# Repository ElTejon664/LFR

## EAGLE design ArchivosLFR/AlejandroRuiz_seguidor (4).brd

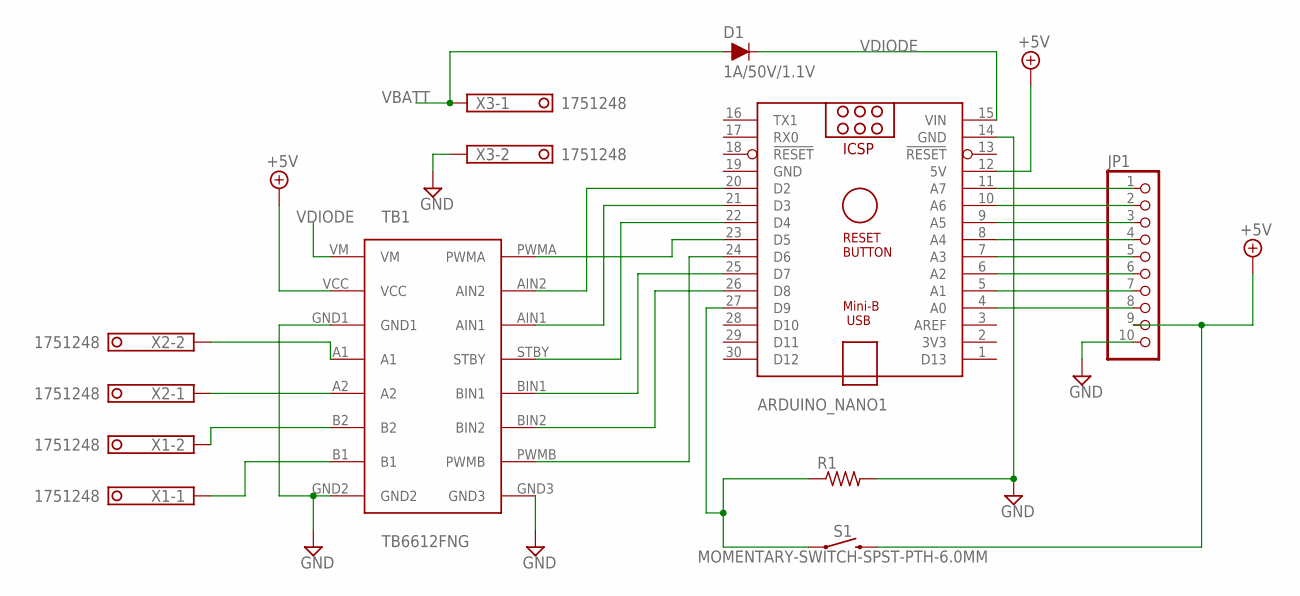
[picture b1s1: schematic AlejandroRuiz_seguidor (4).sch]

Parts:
ARDUINO_NANO1: ARDUINO_NANO
D1: 1A/50V/1.1V; DIODE-1N4001
JP1: PINHD-1X10; 1X10
R1: R-US_0204/5; 0204/5
S1: MOMENTARY-SWITCH-SPST-PTH-6.0MM; TACTILE_SWITCH_PTH_6.0MM
TB1: TB6612FNG
X1, X2, X3: 1751248

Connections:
+5V: ARDUINO_NANO1.12 (5V), JP1.9, S1.3 (2), TB1.VCC
GND: ARDUINO_NANO1.14 (GND), ARDUINO_NANO1.19 (GND), JP1.10, R1.2, TB1.GND1, TB1.GND2, TB1.GND3, X3.2
unnamed: ARDUINO_NANO1.24 (D6), TB1.PWMB
unnamed: ARDUINO_NANO1.23 (D5), TB1.PWMA
unnamed: ARDUINO_NANO1.20 (D2), TB1.AIN2
unnamed: ARDUINO_NANO1.21 (D3), TB1.AIN1
unnamed: ARDUINO_NANO1.22 (D4), TB1.STBY
unnamed: ARDUINO_NANO1.25 (D7), TB1.BIN1
unnamed: ARDUINO_NANO1.26 (D8), TB1.BIN2
unnamed: ARDUINO_NANO1.11 (A7), JP1.1
unnamed: ARDUINO_NANO1.10 (A6), JP1.2
unnamed: ARDUINO_NANO1.9 (A5), JP1.3
unnamed: ARDUINO_NANO1.8 (A4), JP1.4
unnamed: ARDUINO_NANO1.7 (A3), JP1.5
unnamed: ARDUINO_NANO1.6 (A2), JP1.6
unnamed: ARDUINO_NANO1.5 (A1), JP1.7
unnamed: ARDUINO_NANO1.4 (A0), JP1.8
unnamed: ARDUINO_NANO1.27 (D9), R1.1, S1.1
unnamed: TB1.A1, X2.2
unnamed: TB1.B2, X1.2
unnamed: TB1.B1, X1.1
unnamed: TB1.A2, X2.1
VBATT: D1.A, X3.1
VDIODE: ARDUINO_NANO1.15 (VIN), D1.C, TB1.VM

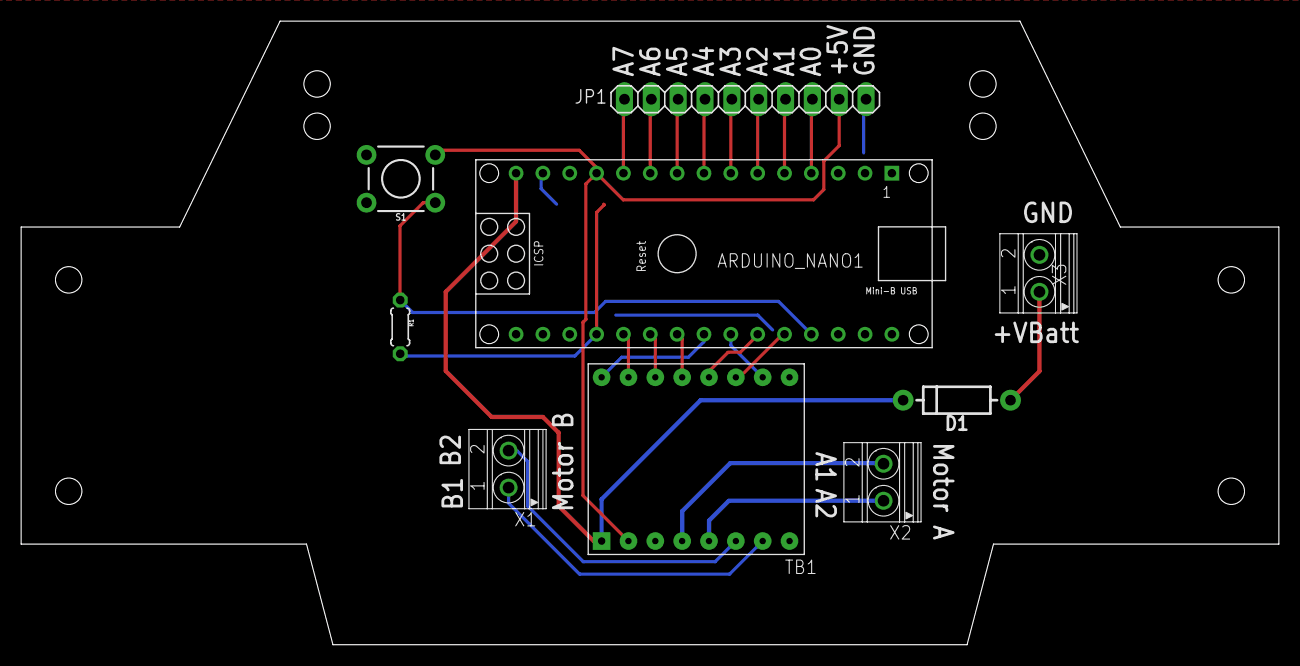
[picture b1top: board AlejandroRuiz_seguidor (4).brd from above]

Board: 2 copper layers, 119.0 x 59.0 mm, 9 parts (0 on the bottom side), 24 nets.

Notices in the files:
parts and their libraries:
SparkFun-Switches: Licensing: Creative Commons ShareAlike 4.0 International - https://creativecommons.org/licenses/by-sa/4.0
